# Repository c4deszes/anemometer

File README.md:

# anemometer
Experiments done to implement a simple and reliable wind speed sensor

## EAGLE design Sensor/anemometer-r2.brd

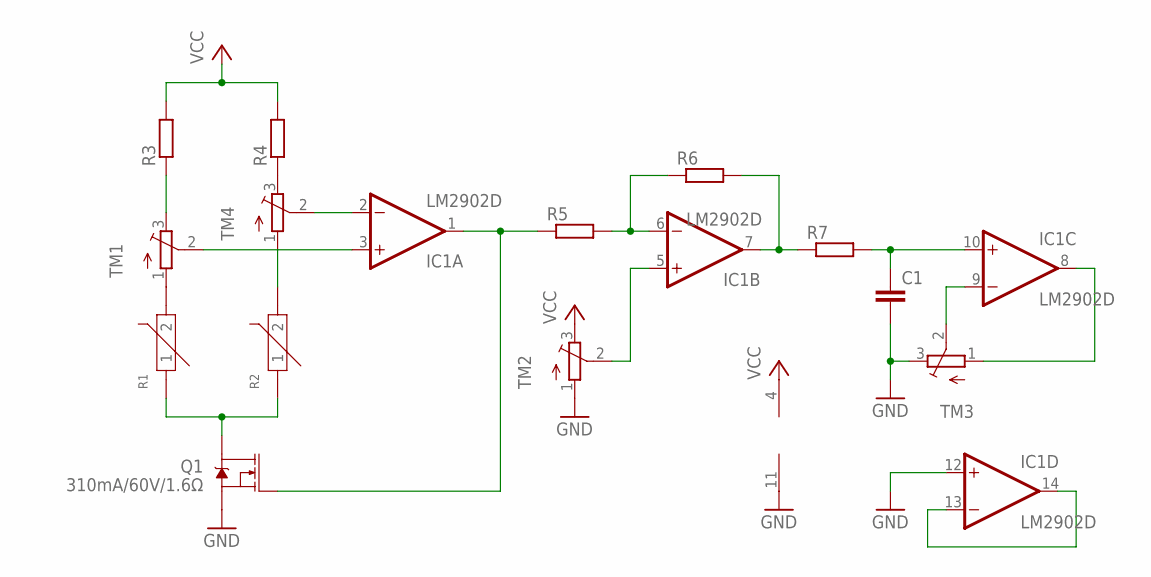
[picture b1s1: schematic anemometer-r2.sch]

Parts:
C1: C-EUC0603; C0603
IC1: LM2902D; SO14
Q1: 310mA/60V/1.6Ω; SOT323
R1, R2: NCP18WF104F03RC; R0603
R3, R4, R5, R6, R7: R-EU_R0603; R0603
TM1, TM2, TM3, TM4: TRIMPOTTC33X; TC33X

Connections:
GND: C1.2, IC1.11 (V-), IC1.12 (+IN), Q1.2 (S), TM2.1 (A), TM3.3 (E)
unnamed: Q1.3 (D), R1.1, R2.1
unnamed: R1.2, TM1.1 (A)
unnamed: R2.2, TM4.1 (A)
unnamed: IC1.3 (+IN), TM1.2 (S)
unnamed: IC1.2 (-IN), TM4.2 (S)
unnamed: R4.1, TM4.3 (E)
unnamed: R3.1, TM1.3 (E)
unnamed: IC1.6 (-IN), R5.2, R6.1
unnamed: IC1.5 (+IN), TM2.2 (S)
unnamed: IC1.1 (OUT), Q1.1 (G), R5.1
unnamed: IC1.7 (OUT), R6.2, R7.1
unnamed: C1.1, IC1.10 (+IN), R7.2
unnamed: IC1.9 (-IN), TM3.2 (S)
unnamed: IC1.8 (OUT), TM3.1 (A)
unnamed: IC1.13 (-IN), IC1.14 (OUT)
VCC: IC1.4 (V+), R3.2, R4.2, TM2.3 (E)

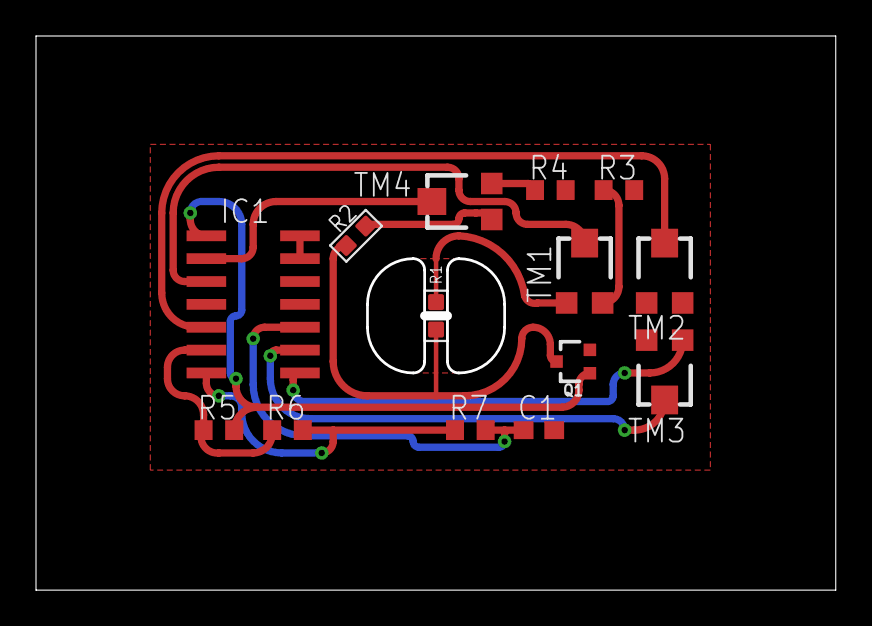
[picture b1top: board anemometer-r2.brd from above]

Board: 2 copper layers, 43.9 x 30.3 mm, 14 parts (0 on the bottom side), 17 nets.

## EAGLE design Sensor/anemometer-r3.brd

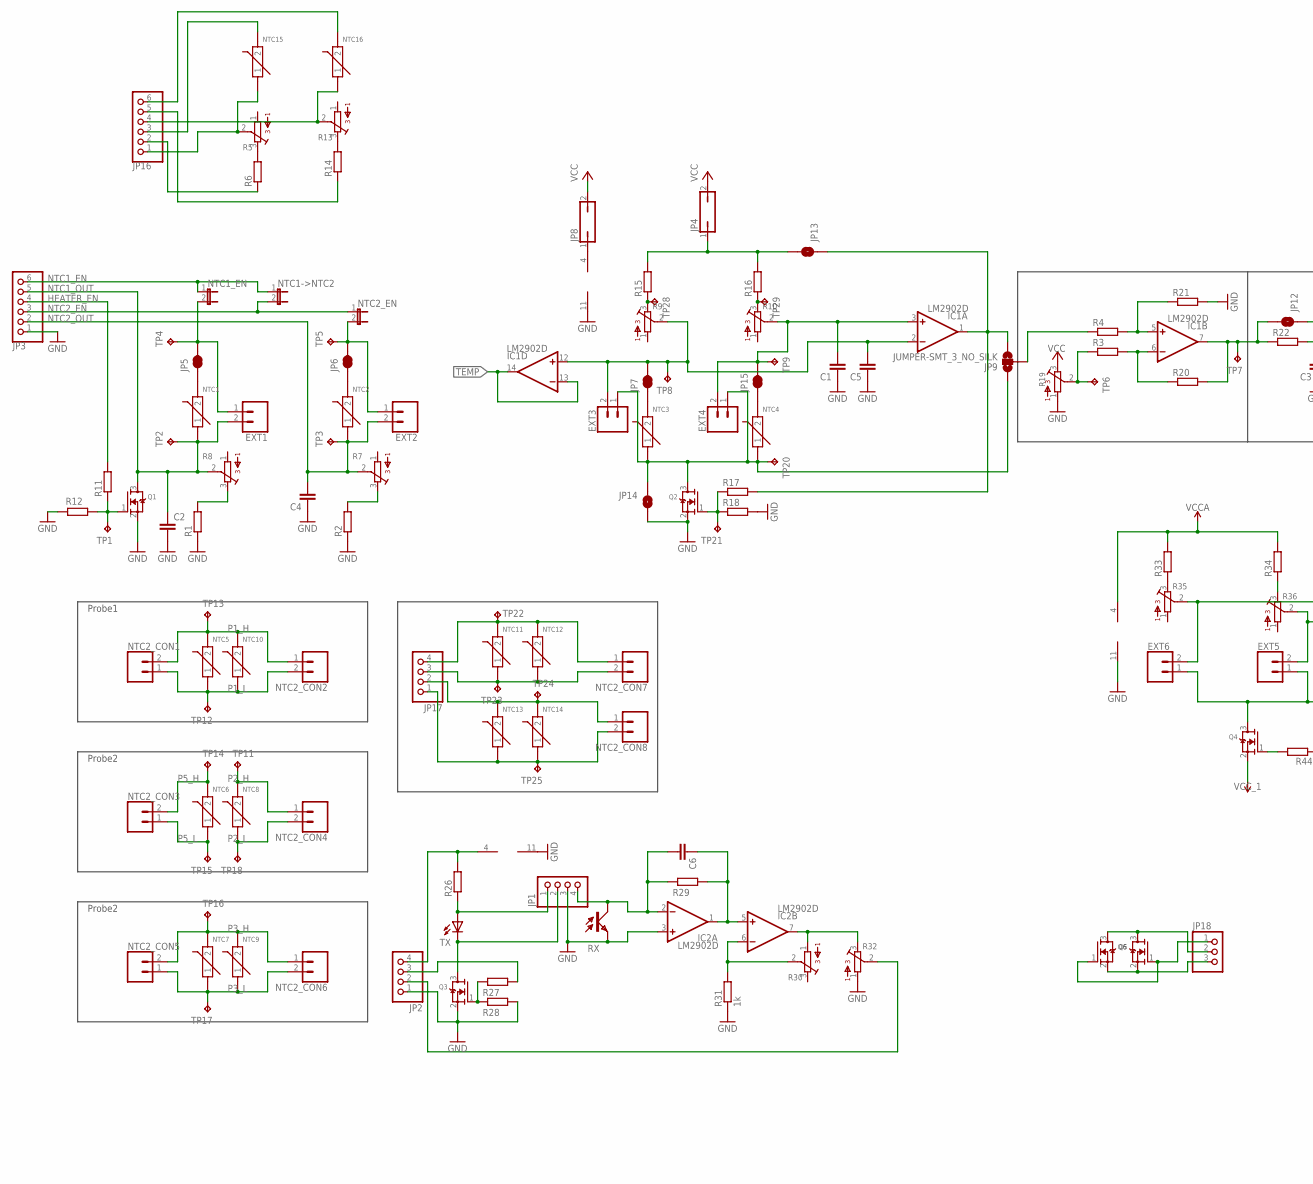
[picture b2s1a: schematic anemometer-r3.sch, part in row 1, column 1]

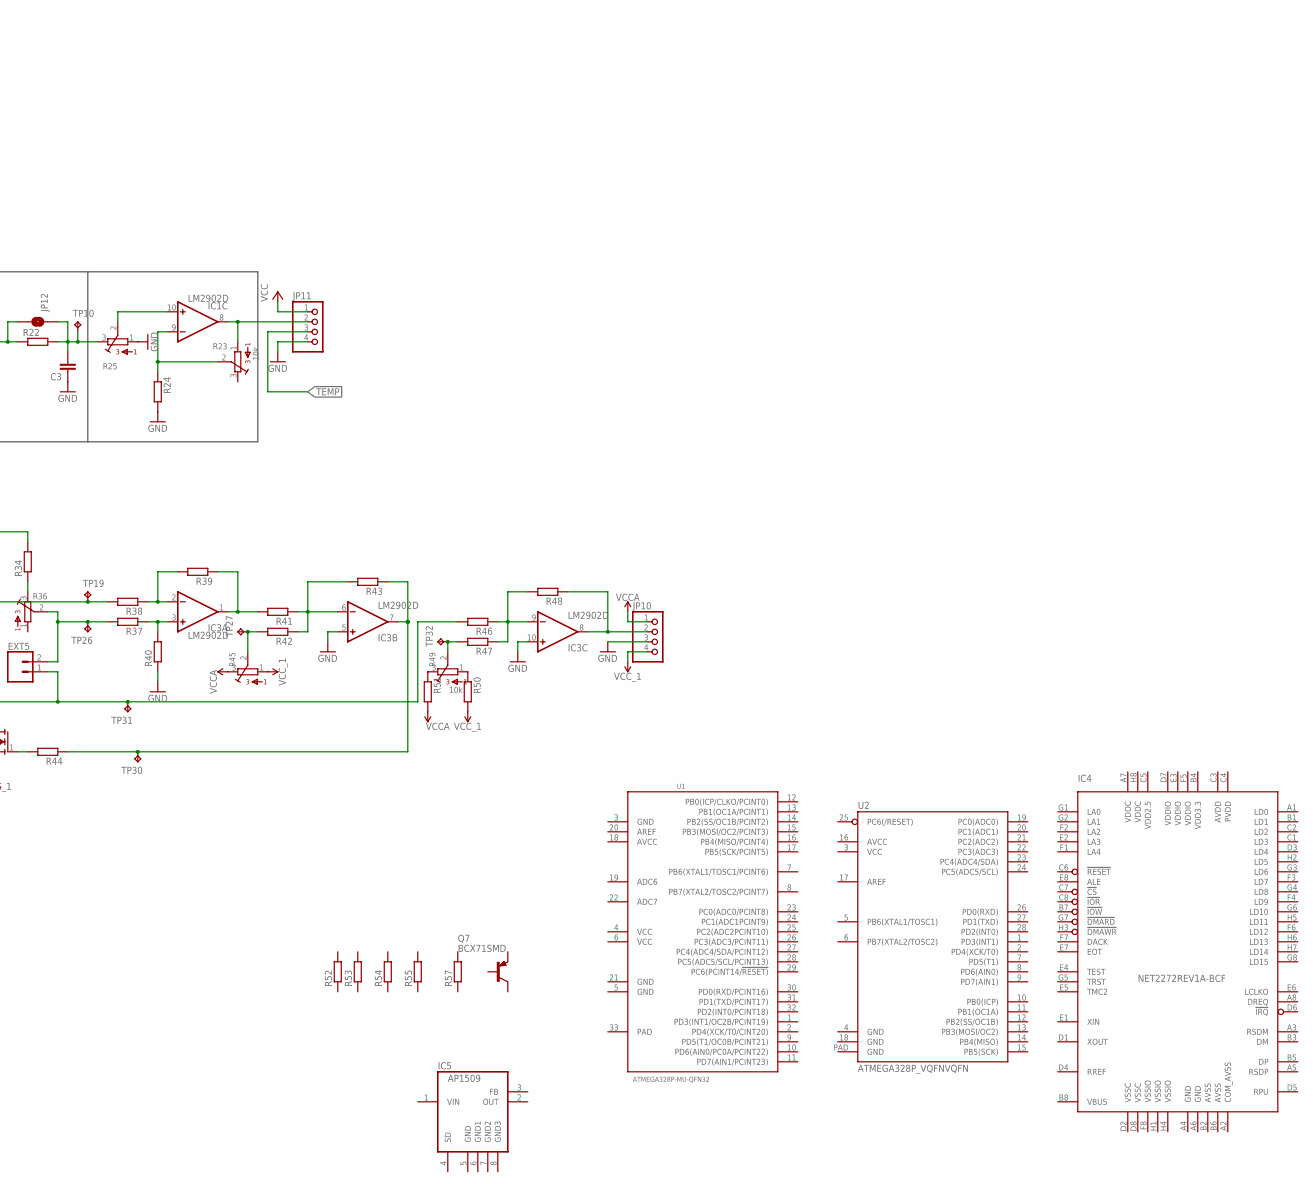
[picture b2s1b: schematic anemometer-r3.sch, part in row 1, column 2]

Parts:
C1, C2, C3, C4, C5, C6: C-EUC0603; C0603
EXT1, EXT2, EXT3, EXT4, EXT5, EXT6: CONN_02; 1X02
IC1, IC2, IC3: LM2902D; SO14
IC4: NET2272REV1A-BCF; FBGA64
IC5: AP1509SOIC-8-TIGHT; SO08-H
JP1, JP2, JP10, JP11, JP17: PINHD-1X4; 1X04
JP3, JP16: PINHD-1X6; 1X06
JP4, JP8: JP1Q; JP1
JP5, JP6, JP7, JP15: JUMPER-SMT_2_NC_TRACE_SILK; SMT-JUMPER_2_NC_TRACE_SILK
JP9: JUMPER-SMT_3_NO_SILK; SMT-JUMPER_3_NO_SILK
JP12, JP13, JP14: JUMPER-SMT_2_NO_SILK; SMT-JUMPER_2_NO_SILK
JP18: PINHD-1X3; 1X03
NTC1, NTC2, NTC3, NTC4, NTC5, NTC6, NTC7, NTC8, NTC9, NTC10, NTC11, NTC12, NTC13, NTC14, NTC15, NTC16: NCP18WF104F03RC; R0603
NTC1->NTC2, NTC1_EN, NTC2_EN: JP1E; JP1
NTC2_CON1, NTC2_CON2, NTC2_CON3, NTC2_CON4, NTC2_CON5, NTC2_CON6, NTC2_CON7, NTC2_CON8: CONN_02; 1X02
Q1, Q2, Q3, Q4, Q5, Q6: MOSFET-NREFLOW; SOT23
Q7: BCX71SMD; SOT23
R1, R2, R3, R4, R6, R11, R12, R14, R15, R16, R17, R18, R20, R21, R22, R24, R26, R27, R28, R29, R33, R34, R37, R38, R39, R40, R41, R42, R43, R44, R46, R47, R48, R50, R51, R53: R-EU_R0603; R0603
R5, R7, R8, R9, R10, R13, R19, R25, R30, R32, R35, R36, R45: 3362P
R23, R49: 10k; 3362P
R31: 1k; R0603
R52: R-EU_R0402; R0402
R54: R-EU_R0805; R0805
R55: R-EU_R1206; R1206
R57: R-EU_R2010; R2010
RX: LPT80A
TP1, TP2, TP3, TP4, TP5, TP6, TP7, TP8, TP9, TP10, TP11, TP12, TP13, TP14, TP15, TP16, TP17, TP18, TP19, TP20, TP21, TP22, TP23, TP24, TP25, TP26, TP27, TP28, TP29, TP30, TP31, TP32: TPTP16R; TP16R
TX: LEDIRL80A; IRL80A
U1: ATMEGA328P-MU-QFN32; QFN32G-0.5-5X5MM
U2: ATMEGA328P_VQFNVQFN; VQFN-28

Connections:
AVDD: IC4.C3 (AVDD)
AVSS: IC4.B2 (AVSS), IC4.B6 (AVSS)
COM_AVSS: IC4.A2 (COM_AVSS)
FB: IC5.3 (FB)
GND: C1.1, C2.2, C3.1, C4.1, C5.1, IC1.11 (V-), IC2.3 (+IN), IC2.11 (V-), IC3.5 (+IN), IC3.10 (+IN), IC3.11 (V-), IC4.A4 (GND), IC4.A6 (GND), IC5.5 (GND), JP1.3, JP2.1, JP3.1, JP10.3, JP11.4, JP14.2, Q1.2 (S), Q2.2 (S), Q3.2 (S), R1.1, R2.1, R12.2, R18.2, R19.1, R21.2, R24.2, R25.1, R28.2, R31.1, R32.1, R40.1, RX.E
GND3: IC5.8 (GND3)
HEATER_EN: JP3.4, R11.2
unnamed: IC1.10 (+IN), R25.2
unnamed: R9.3, R15.1, TP28.TP
unnamed: R10.3, R16.1, TP29.TP
unnamed: R1.2, R8.3
unnamed: JP1.1, R26.1, TX.A
unnamed: JP7.1, NTC3.2
unnamed: Q1.1 (G), R11.1, R12.1, TP1.TP
unnamed: JP16.4, NTC16.1, R13.2
unnamed: R2.2, R7.3
unnamed: JP1.2, Q3.3 (D), TX.K (C)
unnamed: EXT3.1, EXT4.1, JP9.1, JP14.1, NTC3.1, NTC4.1, Q2.3 (D), TP20.TP
unnamed: Q2.1 (G), R17.1, R18.1, TP21.TP
unnamed: IC1.1 (OUT), JP9.3, JP13.1, R17.2
unnamed: IC1.5 (+IN), R4.2, R21.1
unnamed: C3.2, JP12.1, R22.2, R25.3, TP10.TP
unnamed: IC1.6 (-IN), R3.2, R20.1
unnamed: R3.1, R19.2, TP6.TP
unnamed: IC1.9 (-IN), R23.2, R24.1
unnamed: C5.2, EXT3.2, IC1.2 (-IN), IC1.12 (+IN), JP7.2, R9.2, TP8.TP
unnamed: IC1.8 (OUT), JP11.2, R23.1
unnamed: C1.2, EXT4.2, IC1.3 (+IN), JP15.2, R10.2, TP9.TP
unnamed: JP5.1, NTC1.2
unnamed: JP6.1, NTC2.2
unnamed: IC2.4 (V+), JP2.4, R26.2
unnamed: IC1.4 (V+), JP8.1
unnamed: JP17.4, NTC2_CON7.1, NTC11.2, NTC12.2, TP22.TP
unnamed: JP4.1, JP13.2, R15.2, R16.2
unnamed: IC1.7 (OUT), JP12.2, R20.2, R22.1, TP7.TP
unnamed: EXT2.1, JP6.2, NTC2_EN.2, TP5.TP
unnamed: JP17.3, NTC2_CON7.2, NTC11.1, NTC12.1, TP23.TP
unnamed: EXT1.1, JP5.2, NTC1_EN.2, TP4.TP
unnamed: JP15.1, NTC4.2
unnamed: JP17.2, NTC2_CON8.1, NTC13.2, NTC14.2, TP24.TP
unnamed: JP17.1, NTC2_CON8.2, NTC13.1, NTC14.1, TP25.TP
unnamed: R33.1, R35.3
unnamed: JP16.6, NTC16.2
unnamed: JP16.3, NTC15.2
unnamed: Q3.1 (G), R27.2, R28.1
unnamed: JP2.3, R27.1
unnamed: R5.3, R6.2
unnamed: R13.3, R14.2
unnamed: JP16.1, NTC15.1, R5.2
unnamed: C6.1, IC2.1 (OUT), IC2.5 (+IN), R29.1
unnamed: JP16.2, R6.1
unnamed: JP16.5, R14.1
unnamed: C6.2, IC2.2 (-IN), JP1.4, R29.2, RX.C
unnamed: IC2.6 (-IN), R30.2, R31.2
unnamed: IC2.7 (OUT), R30.1, R32.3
unnamed: JP2.2, R32.2
unnamed: R34.1, R36.3
unnamed: JP9.2, R4.1
unnamed: EXT6.2, R35.2, R38.2, TP19.TP
unnamed: EXT5.2, R36.2, R37.2, TP26.TP
unnamed: EXT5.1, EXT6.1, Q4.3 (D), R46.2, TP31.TP
unnamed: IC3.3 (+IN), R37.1, R40.2
unnamed: IC3.2 (-IN), R38.1, R39.2
unnamed: IC3.6 (-IN), R41.1, R42.1, R43.2
unnamed: IC3.1 (OUT), R39.1, R41.2
unnamed: Q4.1 (G), R44.2
unnamed: IC3.7 (OUT), R43.1, R44.1, TP30.TP
unnamed: R49.1, R50.1
unnamed: R42.2, R45.2, TP27.TP
unnamed: IC3.9 (-IN), R46.1, R47.1, R48.2
unnamed: R49.3, R51.1
unnamed: JP18.2, Q5.3 (D), Q6.3 (D)
unnamed: R47.2, R49.2, TP32.TP
unnamed: IC3.8 (OUT), JP10.2, R48.1
unnamed: JP18.3, Q5.2 (S), Q6.2 (S)
unnamed: JP18.1, Q5.1 (G), Q6.1 (G)
NTC1_EN: JP3.6, NTC1->NTC2.1, NTC1_EN.1
NTC1_OUT: C2.1, EXT1.2, JP3.5, NTC1.1, Q1.3 (D), R8.2, TP2.TP
NTC2_EN: JP3.3, NTC1->NTC2.2, NTC2_EN.1
NTC2_OUT: C4.2, EXT2.2, JP3.2, NTC2.1, R7.2, TP3.TP
OUT: IC5.2 (OUT)
P1_H: NTC2_CON1.2, NTC2_CON2.1, NTC5.2, NTC10.2, TP13.TP
P1_L: NTC2_CON1.1, NTC2_CON2.2, NTC5.1, NTC10.1, TP12.TP
P2_H: NTC2_CON4.1, NTC8.2, TP11.TP
P2_L: NTC2_CON4.2, NTC8.1, TP18.TP
P3_H: NTC2_CON5.2, NTC2_CON6.1, NTC7.2, NTC9.2, TP16.TP
P3_L: NTC2_CON5.1, NTC2_CON6.2, NTC7.1, NTC9.1, TP17.TP
P5_H: NTC2_CON3.2, NTC6.2, TP14.TP
P5_L: NTC2_CON3.1, NTC6.1, TP15.TP
PVDD: IC4.C4 (PVDD)
TEMP: IC1.13 (-IN), IC1.14 (OUT), JP11.3
VCC: JP4.2, JP8.2, JP11.1, R19.3
VCCA: IC3.4 (V+), JP10.1, R33.2, R34.2, R45.3, R51.2
VCC_1: JP10.4, Q4.2 (S), R45.1, R50.2
VDD2.5: IC4.C5 (VDD2.5)
VDD3.3: IC4.B4 (VDD3.3)
VDDC: IC4.A7 (VDDC), IC4.H8 (VDDC)
VDDIO: IC4.D7 (VDDIO), IC4.E3 (VDDIO), IC4.F5 (VDDIO)
VSSC: IC4.D2 (VSSC), IC4.D8 (VSSC)
VSSIO: IC4.F8 (VSSIO), IC4.H1 (VSSIO), IC4.H4 (VSSIO)

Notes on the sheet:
Probe1
Probe2

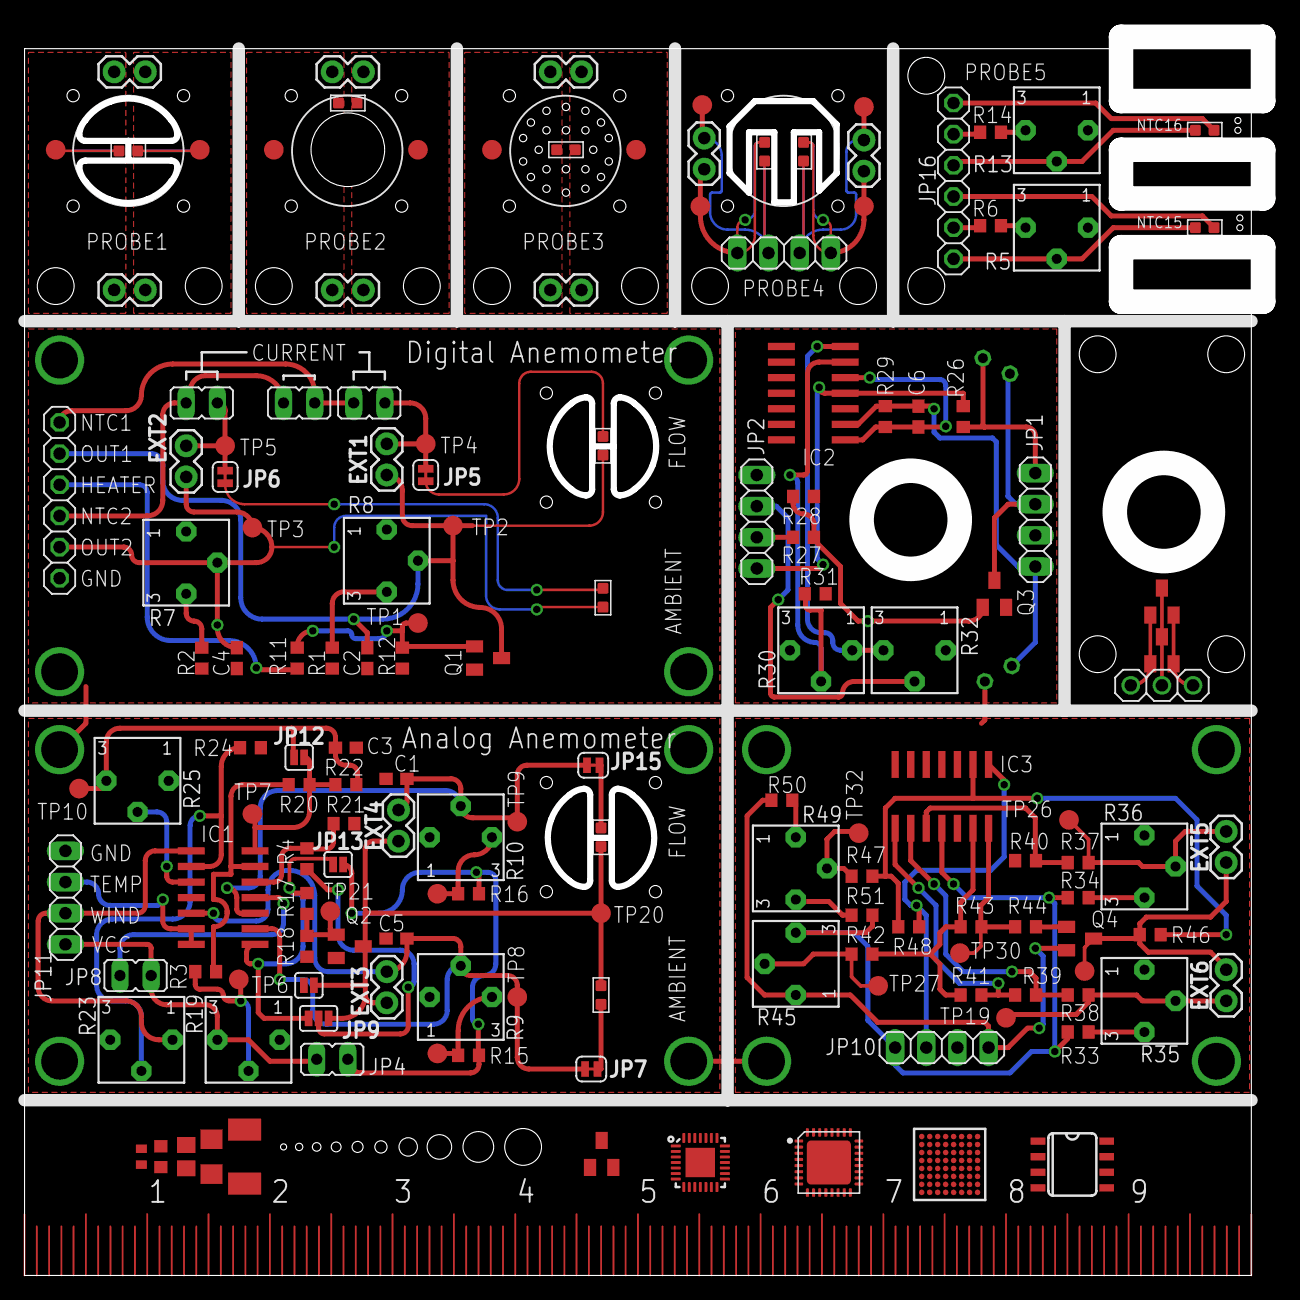
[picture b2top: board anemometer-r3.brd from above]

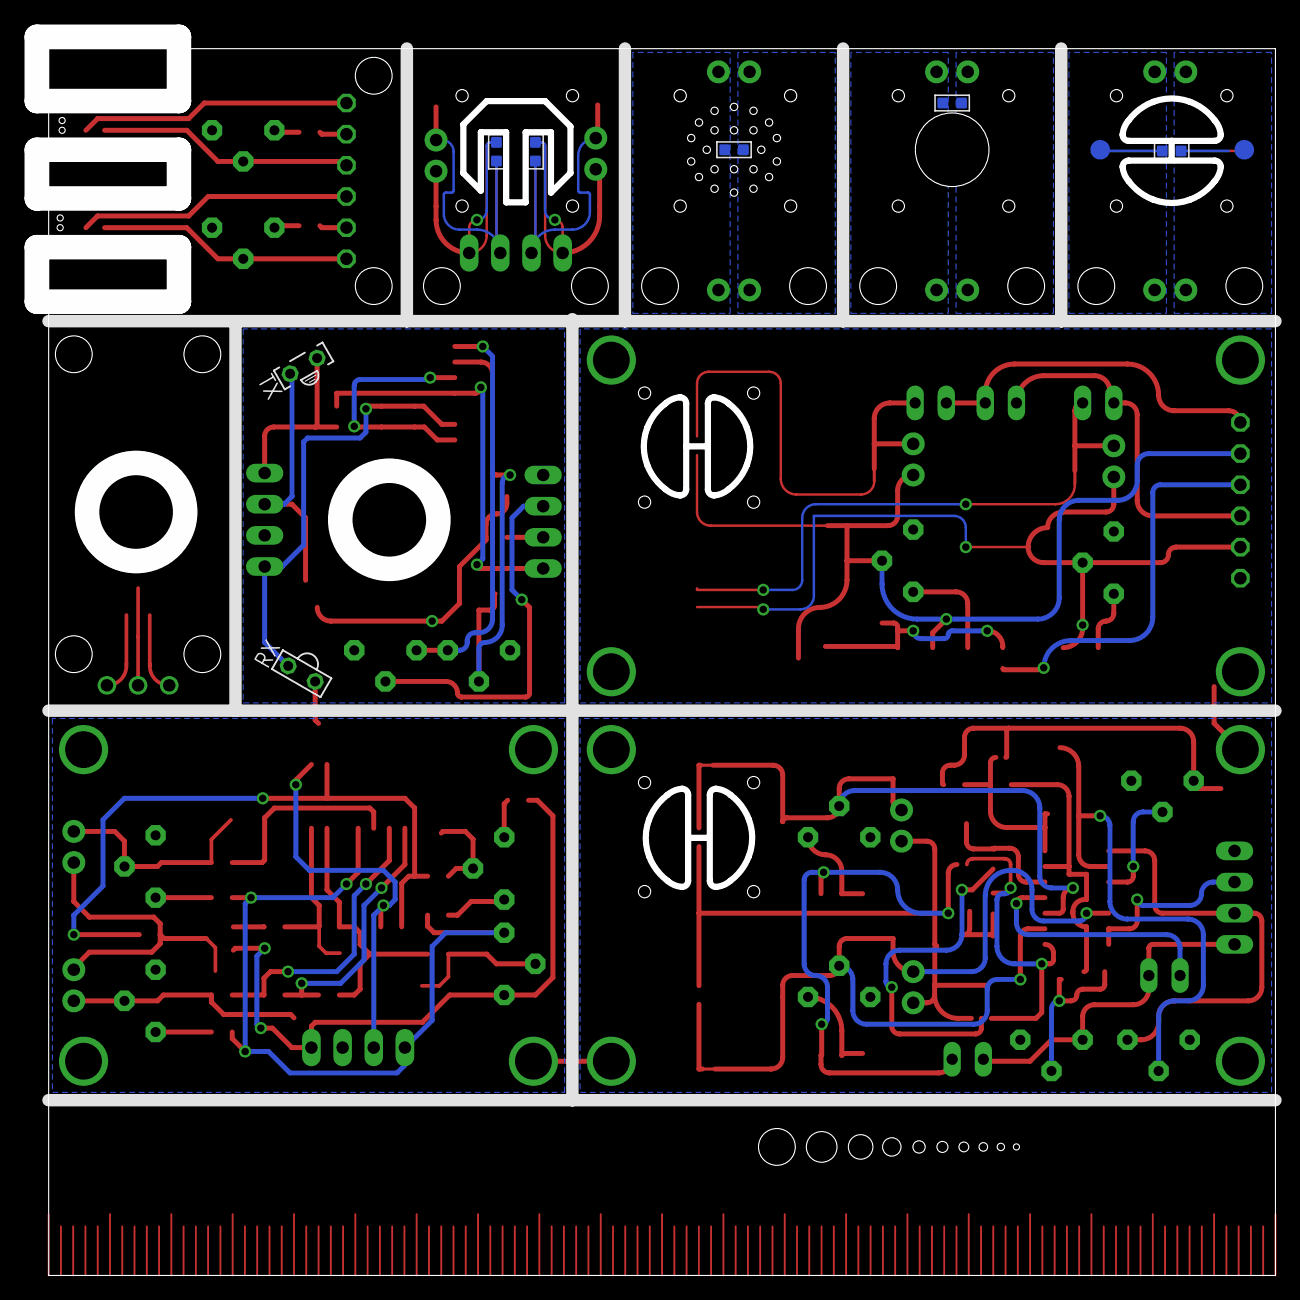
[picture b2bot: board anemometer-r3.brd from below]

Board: 2 copper layers, 100.0 x 100.0 mm, 161 parts (9 on the bottom side), 92 nets.

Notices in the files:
parts and their libraries:
SparkFun-DiscreteSemi: Licensing: Creative Commons ShareAlike 4.0 International - https://creativecommons.org/licenses/by-sa/4.0
plxtech: PCI 9056 Data Book, Version 0.91© 2001 PLX Technology, Inc.
All rights reserved.
